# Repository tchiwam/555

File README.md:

# 555
555 Xmas piano card, led blinker, noise maker ... 

Just solder only 1 of the 5 possible resistors per switch, depending how good you are, go all the way to 0201...

The current BOM is Digikey centric, but should be available from anywhere.

I will add multiple languages greetings if you send them to me.  

The license is Let me know you are making them :)
Thanks for the donations ! You are welcome ;)

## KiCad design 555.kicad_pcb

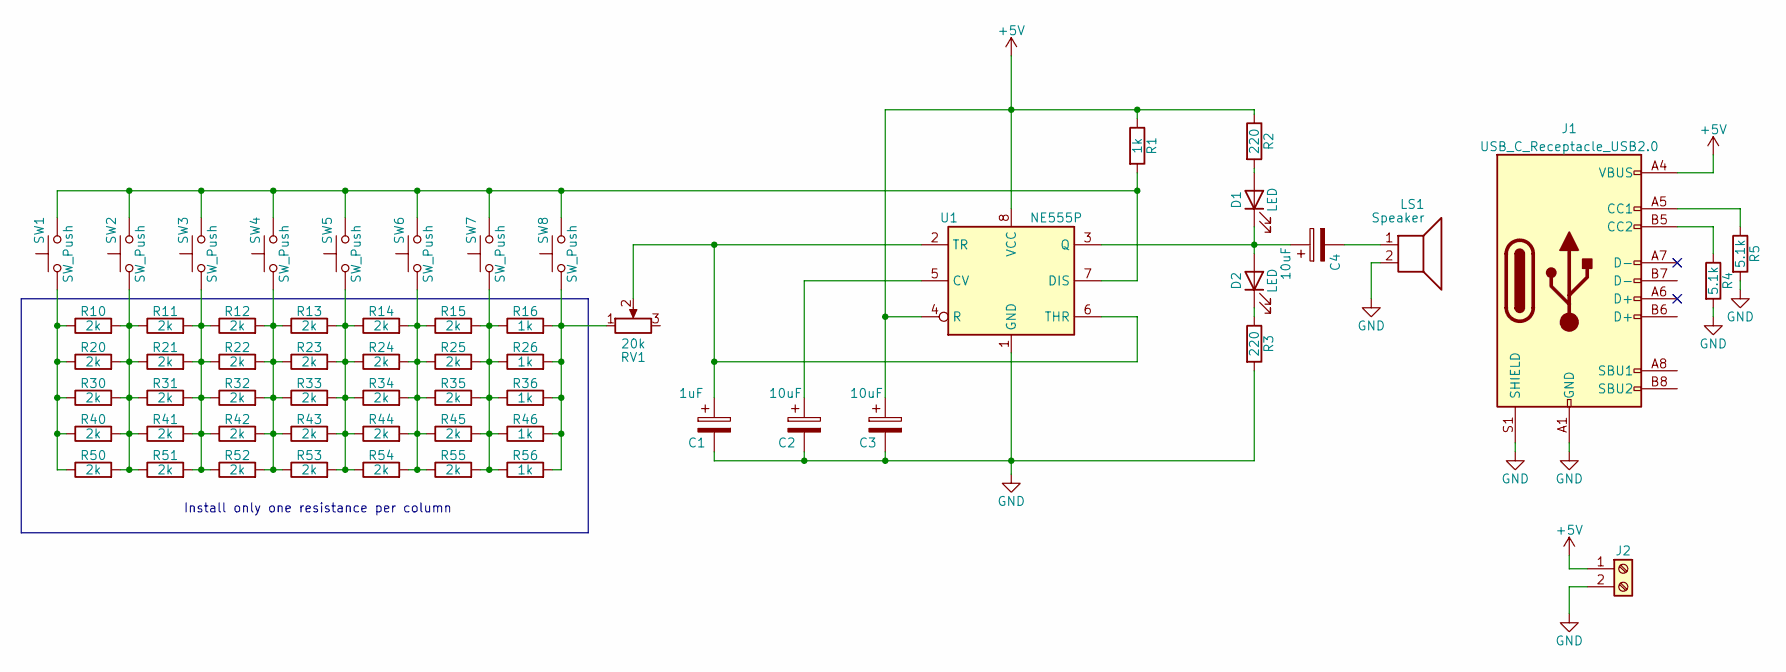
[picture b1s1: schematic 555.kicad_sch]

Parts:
C1: 1uF; CP_Radial_D5.0mm_P2.00mm; Manufacturer part number 732-8625-1-ND
C2, C3, C4: 10uF; CP_Radial_D5.0mm_P2.00mm; Manufacturer part number 732-8625-1-ND
D1: LED; LED_D5.0mm; Manufacturer part number 160-1853-ND
D2: LED; LED_D5.0mm; Manufacturer part number 160-1852-ND
J1: USB_C_Receptacle_USB2.0; USB_C_Receptacle_GCT_USB4085
J2: Screw_Terminal_01x02; TerminalBlock_Phoenix_PT-1,5-2-5.0-H_1x02_P5.00mm_Horizontal
LS1: Speaker; TerminalBlock_Phoenix_PT-1,5-2-5.0-H_1x02_P5.00mm_Horizontal; Manufacturer part number 458-1124-ND
R1, R16: 1k; R_Axial_DIN0207_L6.3mm_D2.5mm_P10.16mm_Horizontal; Manufacturer part number RNF14FTD1K00CT-ND
R2, R3: 220; R_Axial_DIN0207_L6.3mm_D2.5mm_P10.16mm_Horizontal; Manufacturer part number S220CACT-ND
R4, R5: 5.1k; R_Axial_DIN0207_L6.3mm_D2.5mm_P10.16mm_Horizontal; Manufacturer part number RNF14FTD1K00CT-ND
R10, R11, R12, R13, R14, R15: 2k; R_Axial_DIN0207_L6.3mm_D2.5mm_P10.16mm_Horizontal; Manufacturer part number RNF14FTD2K00CT-ND
R20, R21, R22, R23, R24, R25: 2k; R_1206_3216Metric; Manufacturer part number 738-RMCF1206FG2K00CT-ND
R26: 1k; R_1206_3216Metric; Manufacturer part number RNCP1206FTD1K00CT-ND
R30, R31, R32, R33, R34, R35: 2k; R_0603_1608Metric; Manufacturer part number P2.00KHCT-ND
R36: 1k; R_0603_1608Metric; Manufacturer part number RNCP0603FTD1K00CT-ND
R40, R41, R42, R43, R44, R45: 2k; R_0402_1005Metric; Manufacturer part number 541-2.00KLCT-ND
R46: 1k; R_0402_1005Metric; Manufacturer part number 311-1.0KJRCT-ND
R50, R51, R52, R53, R54, R55: 2k; R_0201_0603Metric; Manufacturer part number P123271CT-ND
R56: 1k; R_0201_0603Metric; Manufacturer part number 311-1KMCT-ND
RV1: 20k; Potentiometer_TT_P0915N; Manufacturer part number 987-1277-ND
SW1, SW2, SW3, SW4, SW5, SW6, SW7, SW8: SW_Push; SW_PUSH_6mm; Manufacturer part number 679-2428-ND
U1: NE555P; DIP-8_W7.62mm; Manufacturer part number 296-NE555P-ND

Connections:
+5V: C3.1, J1.A4 (VBUS), J1.A9 (VBUS), J1.B4 (VBUS), J1.B9 (VBUS), J2.1, R1.1, R2.1, U1.4 (R), U1.8 (VCC)
GND: C1.2, C2.2, C3.2, J1.A1 (GND), J1.A12 (GND), J1.B1 (GND), J1.B12 (GND), J1.S1 (SHIELD), J2.2, LS1.2, R3.2, R4.2, R5.2, U1.1 (GND)
unnamed: C1.1, RV1.2, U1.2 (TR), U1.6 (THR)
unnamed: C2.1, U1.5 (CV)
unnamed: C4.1, D1.1 (K), D2.2 (A), U1.3 (Q)
unnamed: C4.2, LS1.1
unnamed: D1.2 (A), R2.2
unnamed: D2.1 (K), R3.1
unnamed: J1.A5 (CC1), R5.1
unnamed: J1.B5 (CC2), R4.1
unnamed: R1.2, SW1.2, SW2.2, SW3.2, SW4.2, SW5.2, SW6.2, SW7.2, SW8.2, U1.7 (DIS)
unnamed: R10.1, R20.1, R30.1, R40.1, R50.1, SW1.1
unnamed: R10.2, R11.1, R20.2, R21.1, R30.2, R31.1, R40.2, R41.1, R50.2, R51.1, SW2.1
unnamed: R11.2, R12.1, R21.2, R22.1, R31.2, R32.1, R41.2, R42.1, R51.2, R52.1, SW3.1
unnamed: R12.2, R13.1, R22.2, R23.1, R32.2, R33.1, R42.2, R43.1, R52.2, R53.1, SW4.1
unnamed: R13.2, R14.1, R23.2, R24.1, R33.2, R34.1, R43.2, R44.1, R53.2, R54.1, SW5.1
unnamed: R14.2, R15.1, R24.2, R25.1, R34.2, R35.1, R44.2, R45.1, R54.2, R55.1, SW6.1
unnamed: R15.2, R16.1, R25.2, R26.1, R35.2, R36.1, R45.2, R46.1, R55.2, R56.1, SW7.1
unnamed: R16.2, R26.2, R36.2, R46.2, R56.2, RV1.1, SW8.1

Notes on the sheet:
Install only one resistance per column

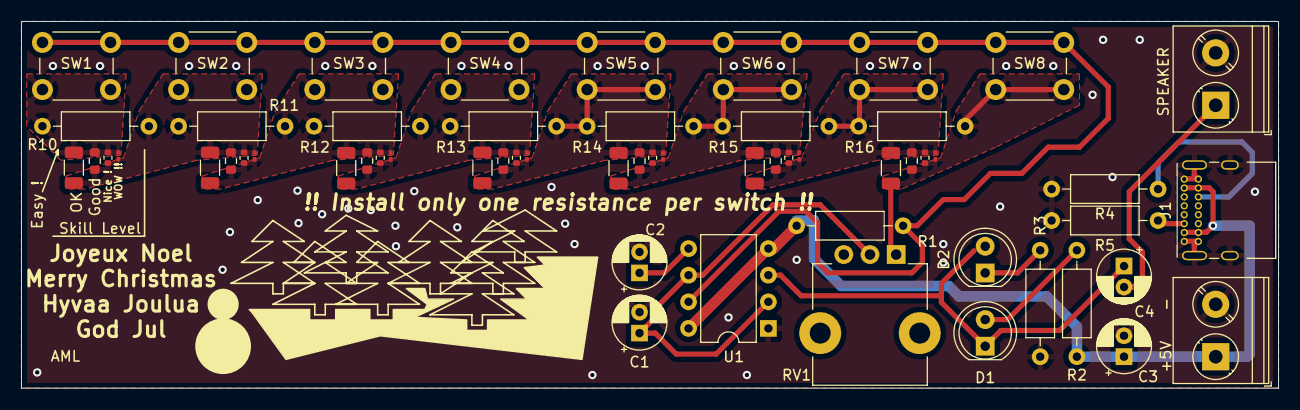
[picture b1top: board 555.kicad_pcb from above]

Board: 2 copper layers, 120.0 x 35.0 mm, 59 parts (0 on the bottom side), 19 nets.

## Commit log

2022-11-27 marked
2022-11-27 Snow on the branches
2022-11-30 Simpler, remove the 10k resistor, move the potentiometer to full to play
2022-11-30 PCB updated
2022-11-30 Prettier sch
2022-12-11 USB-C resistor CC
2022-12-14 Art contribution AML
